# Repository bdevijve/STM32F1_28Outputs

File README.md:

# STM32F1_28Outputs
Carte domotique de Gaël - STM32F103VET6 - 28 sorties NPN 5-24V

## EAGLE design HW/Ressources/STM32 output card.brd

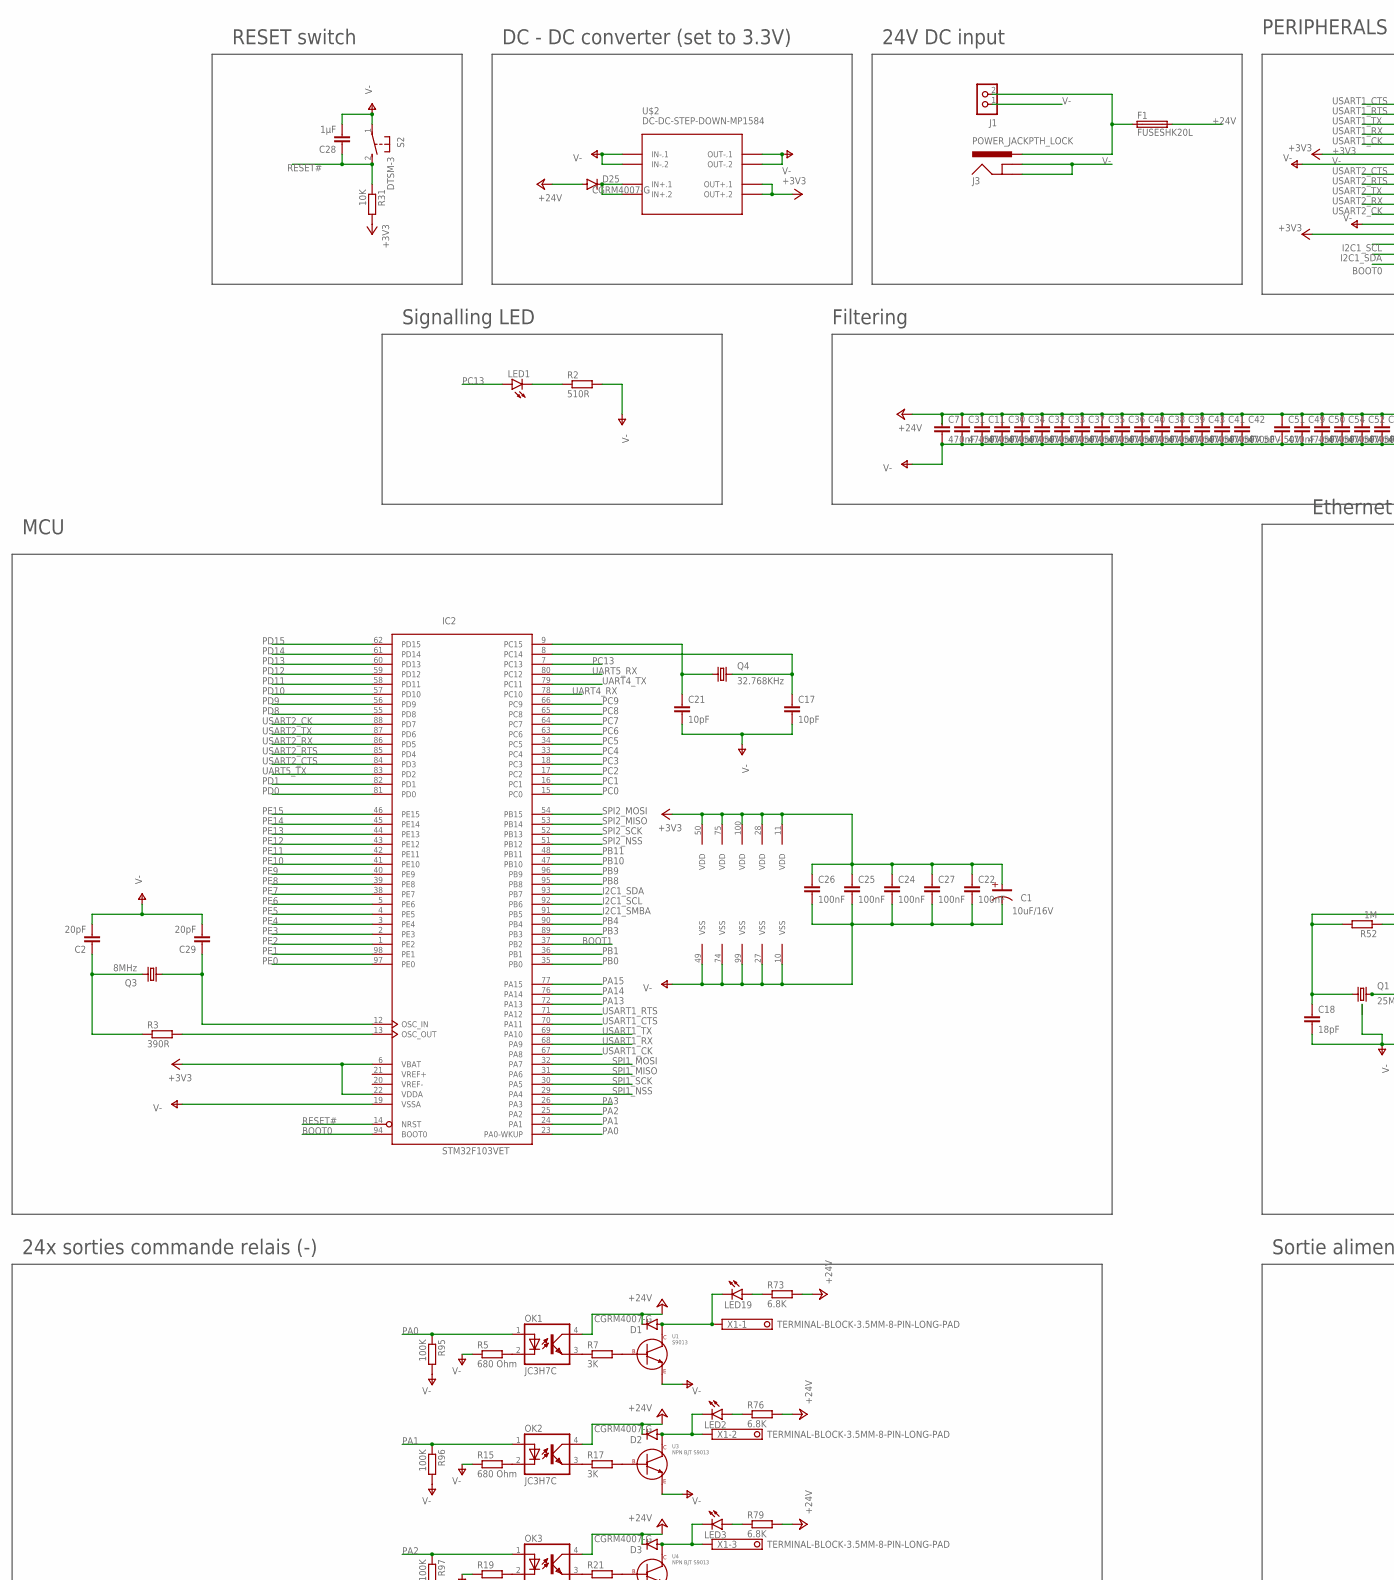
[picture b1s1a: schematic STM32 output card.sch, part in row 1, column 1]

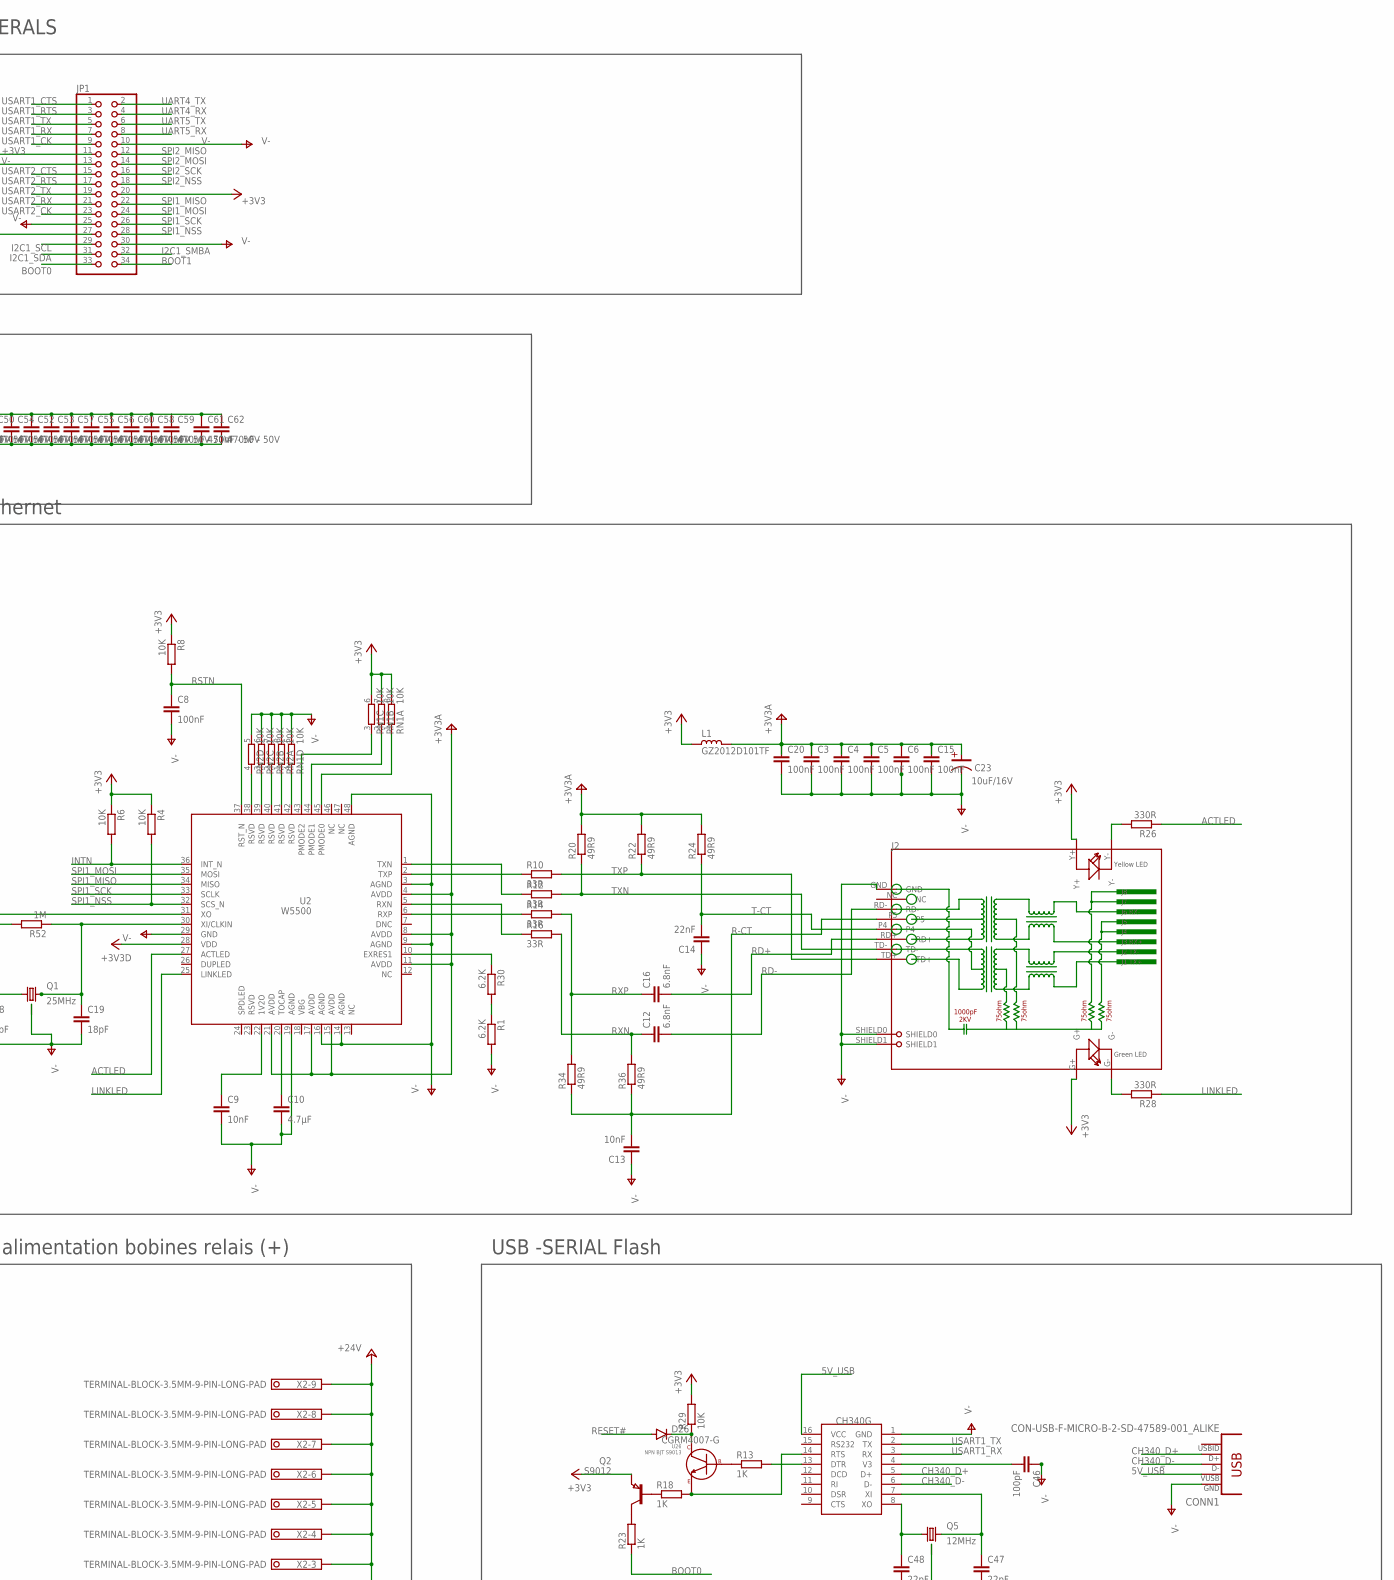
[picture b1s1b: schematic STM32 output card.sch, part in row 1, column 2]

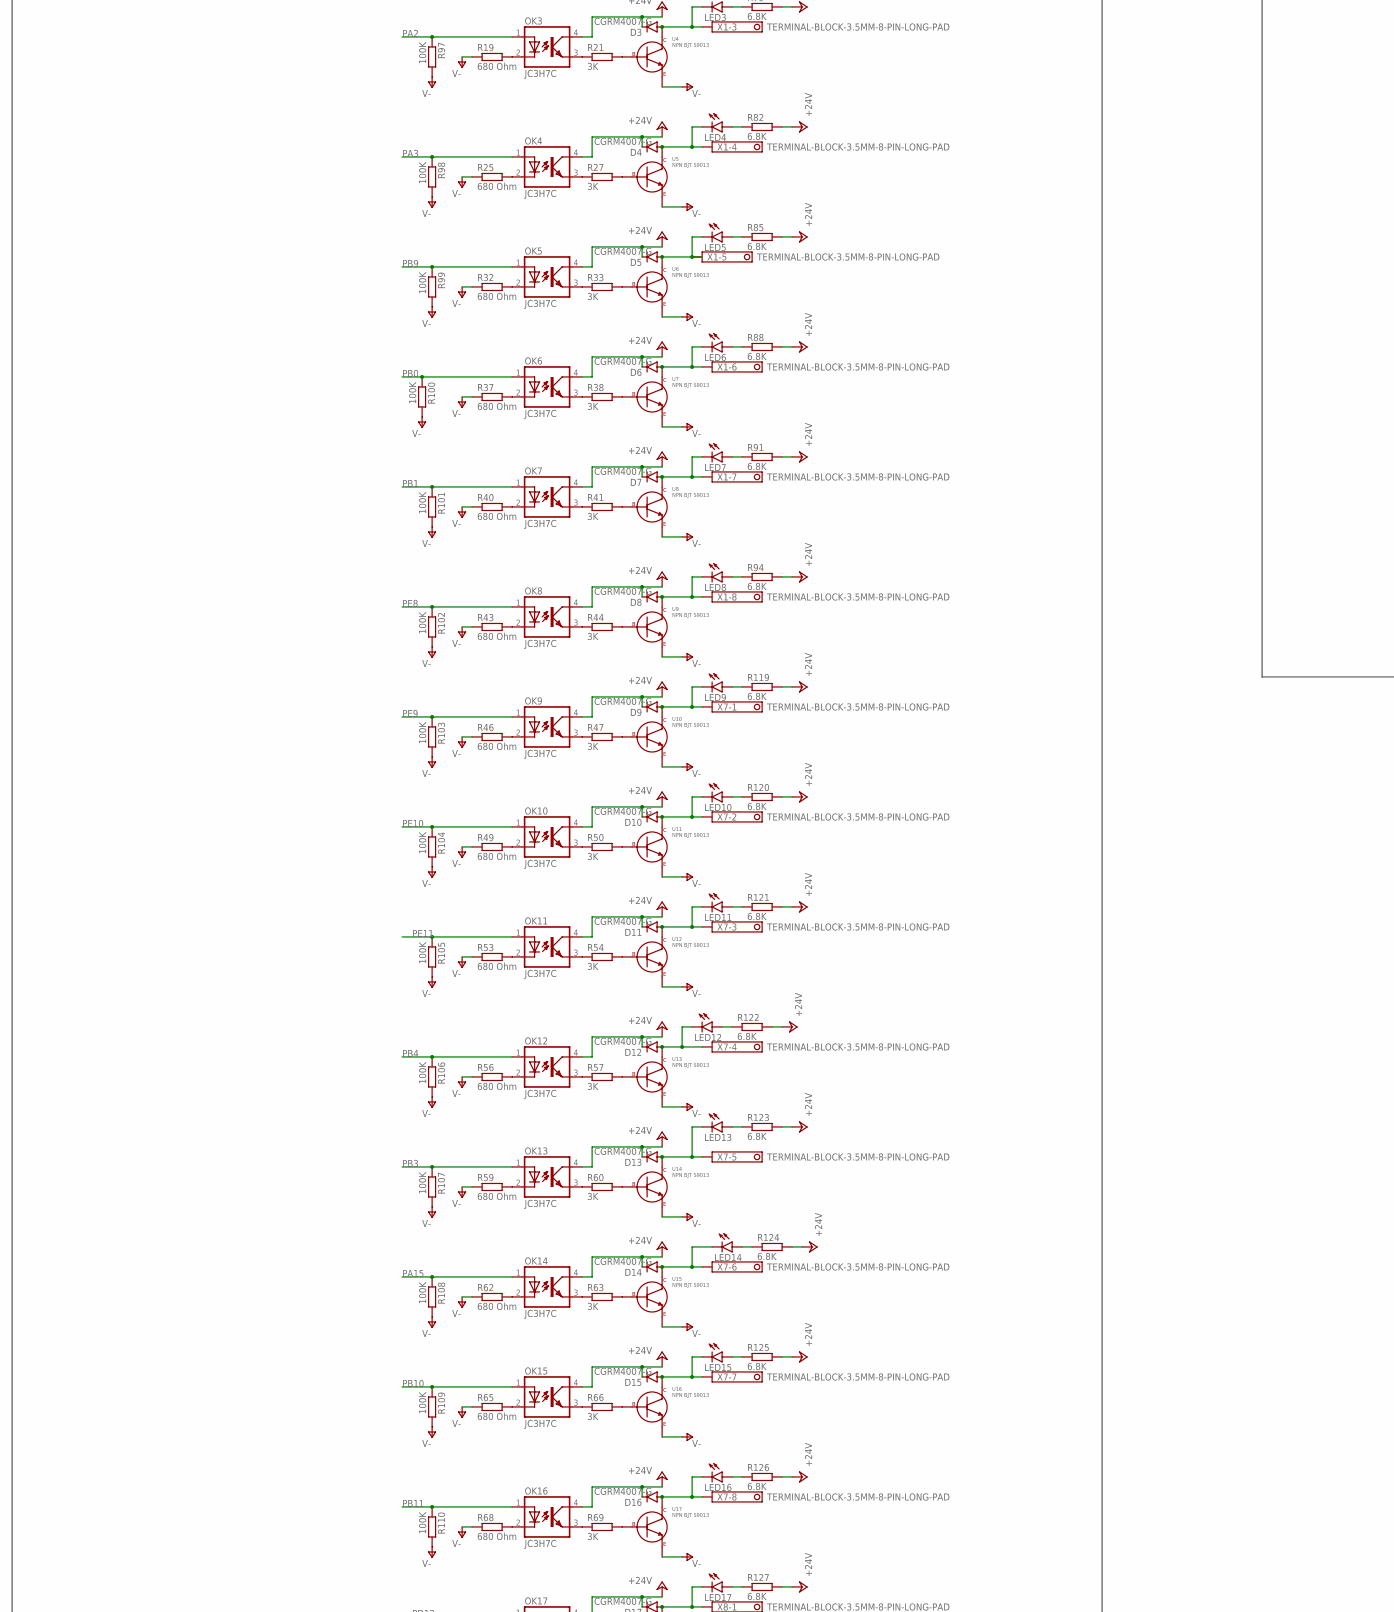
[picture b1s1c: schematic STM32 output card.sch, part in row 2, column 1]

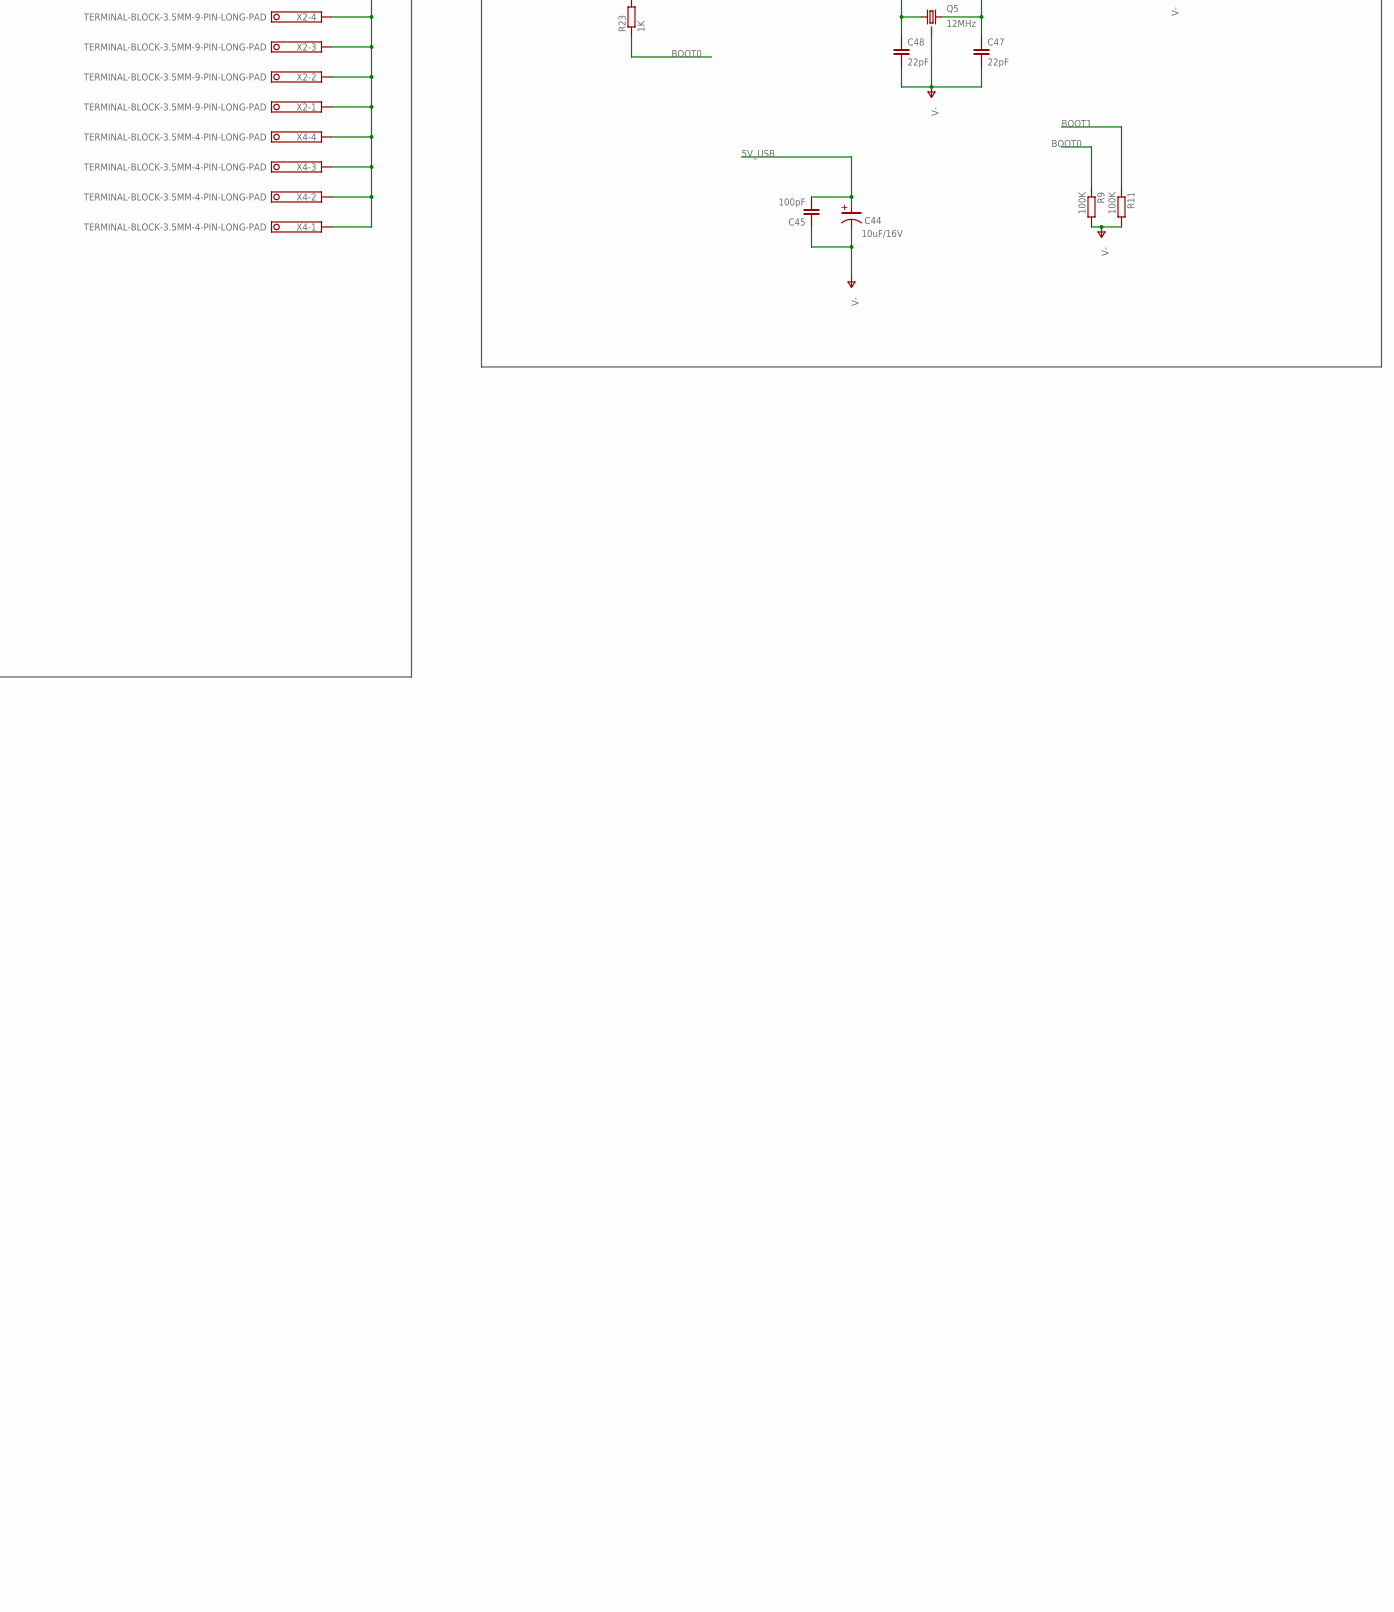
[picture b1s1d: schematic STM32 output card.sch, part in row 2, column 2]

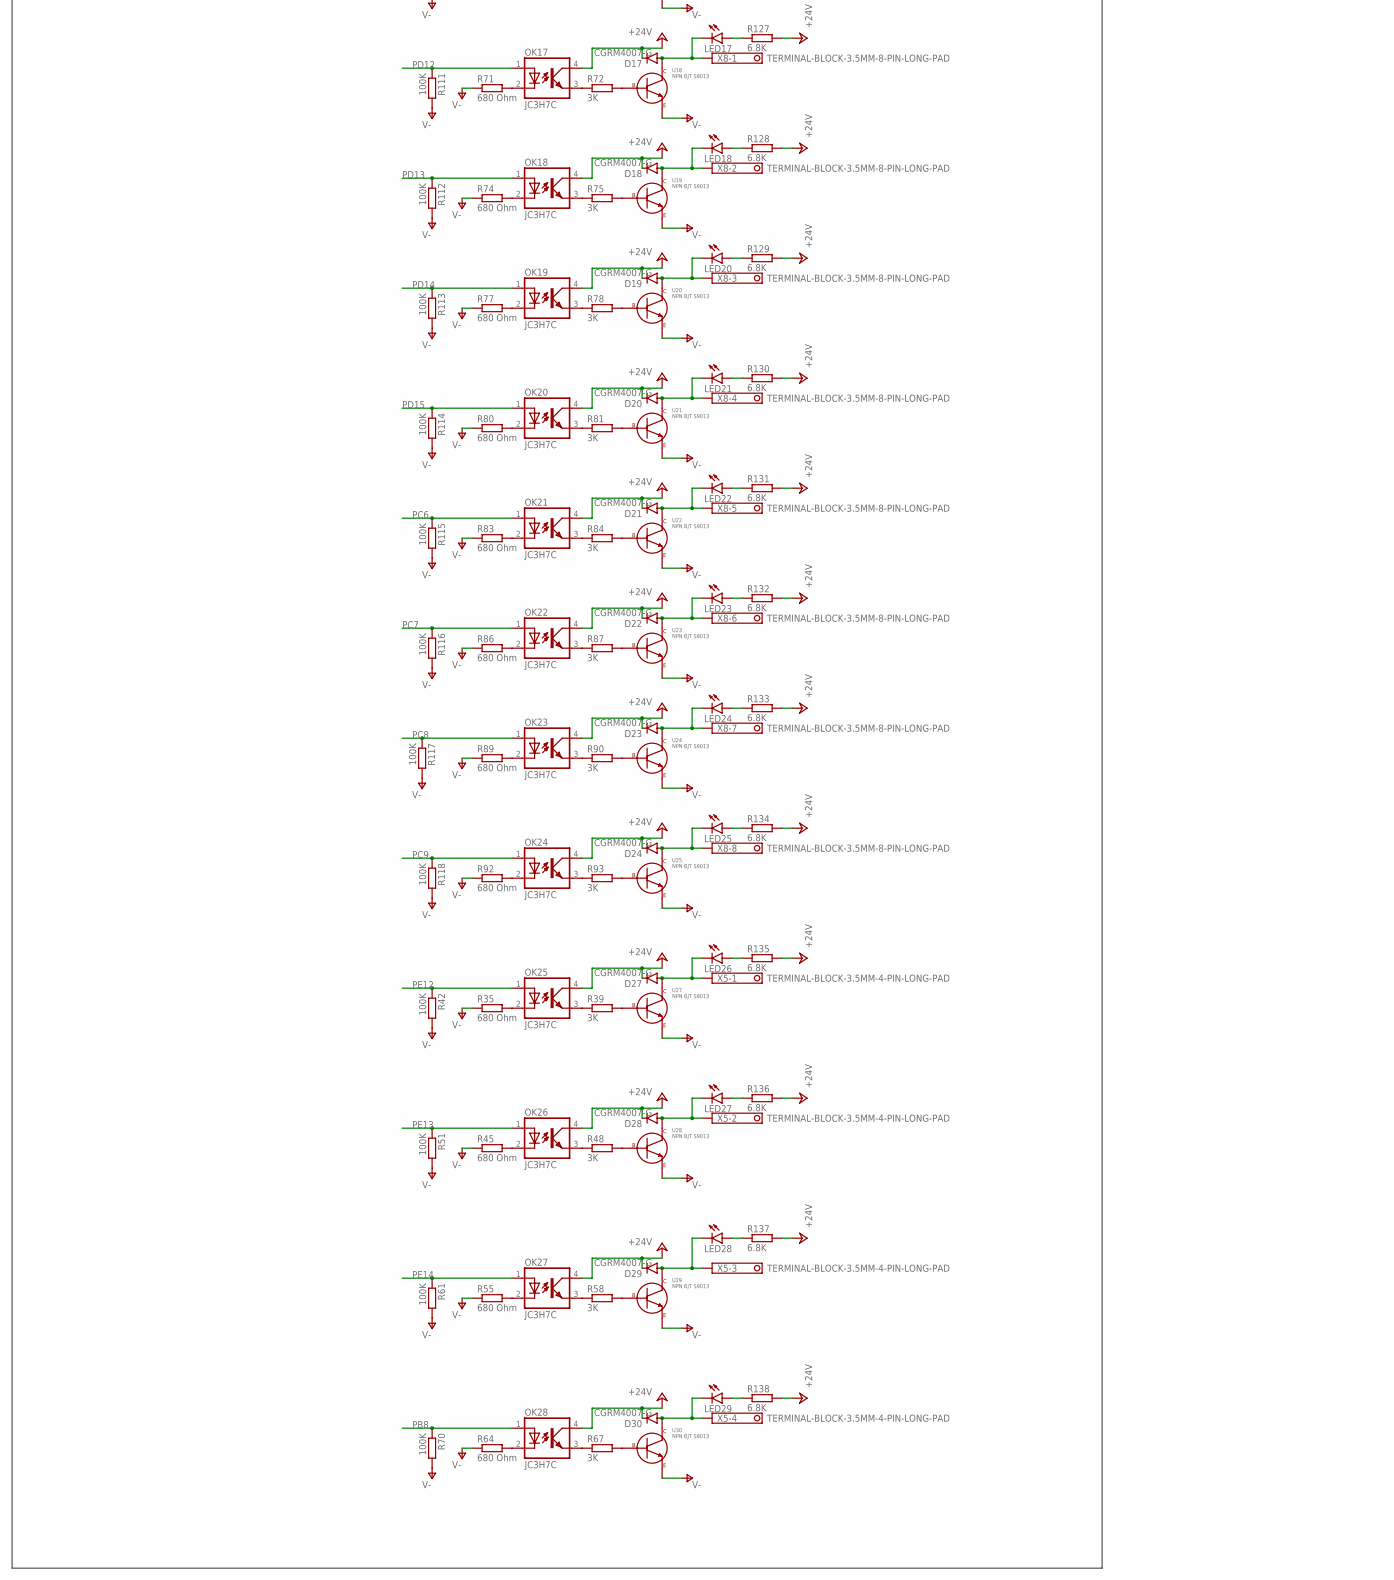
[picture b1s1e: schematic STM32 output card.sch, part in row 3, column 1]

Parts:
C1, C23, C44: 10uF/16V; C-3216(TANTAL)
C2, C29: 20pF; C0402
C3, C4, C5, C6, C8, C15, C20, C22, C24, C25, C26, C27: 100nF; C0402
C7, C11, C30, C31, C32, C33, C34, C35, C36, C37, C38, C39, C40, C41, C42, C43, C49, C50, C51, C52, C53, C54, C55, C56, C57, C58, C59, C60, C61, C62: 470nF - 50V; C0805
C9, C13: 10nF; C0402
C10: 4.7µF; C0402
C12, C16: 6.8nF; C0402
C14: 22nF; C0402
C17, C21: 10pF; C0402
C18, C19: 18pF; C0402
C28: 1µF; C0402
C45, C46: 100pF; C0402
C47, C48: 22pF; C0402
CONN1: CON-USB-F-MICRO-B-2-SD-47589-001_ALIKE; CON_USB_MICRO-B-3
D1, D2, D3, D4, D5, D6, D7, D8, D9, D10, D11, D12, D13, D14, D15, D16, D17, D18, D19, D20, D21, D22, D23, D24, D25, D26, D27, D28, D29, D30: CGRM4007-G; SOD-123_MINI-SMA
F1: FUSESHK20L; SHK20L
IC2: STM32F103VET; LQFP100
J1: CON_TERMINAL_BLOCK_02-5MM; TERMINAL_BLOCK_2P_5
J2: RJ45-HR911105A-HR911105A; RJ45
J3: POWER_JACKPTH_LOCK; POWER_JACK_PTH_LOCK
JP1: PINHD-2X17; 2X17
L1: GZ2012D101TF; L0805
LED1: LEDCHIP-LED0603; CHIP-LED0603
LED2, LED3, LED4, LED5, LED6, LED7, LED8, LED9, LED10, LED11, LED12, LED13, LED14, LED15, LED16, LED17, LED18, LED19, LED20, LED21, LED22, LED23, LED24, LED25, LED26, LED27, LED28, LED29: LEDSML0603; SML0603
OK1, OK2, OK3, OK4, OK5, OK6, OK7, OK8, OK9, OK10, OK11, OK12, OK13, OK14, OK15, OK16, OK17, OK18, OK19, OK20, OK21, OK22, OK23, OK24, OK25, OK26, OK27, OK28: JC3H7C; MINI-FLAT-4
Q1: 25MHz; 3.2X2.5_KX-7
Q2: S9012; SOT23
Q3: 8MHz; 5.0X3.2_2
Q4: 32.768KHz; 3.2X1.5
Q5: 12MHz; 3.2X2.5_KX-7
R1, R30: 6.2K; R0603
R2: 510R; R0402
R3: 390R; R0603
R4, R6, R8, R29, R31: 10K; R0402
R5, R15, R19, R25, R32, R35, R37, R40, R43, R45, R46, R49, R53, R55, R56, R59, R62, R64, R65, R68, R71, R74, R77, R80, R83, R86, R89, R92: 680 Ohm; R0402
R7, R17, R21, R27, R33, R38, R39, R41, R44, R47, R48, R50, R54, R57, R58, R60, R63, R66, R67, R69, R72, R75, R78, R81, R84, R87, R90, R93: 3K; R0805
R9, R11, R42, R51, R61, R70, R95, R96, R97, R98, R99, R100, R101, R102, R103, R104, R105, R106, R107, R108, R109, R110, R111, R112, R113, R114, R115, R116, R117, R118: 100K; R0402
R10, R12, R14, R16: 33R; R0805
R13, R18, R23: 1K; R0402
R20, R22, R24, R34, R36: 49R9; R0805
R26, R28: 330R; R0402
R52: 1M; R0402
R73, R76, R79, R82, R85, R88, R91, R94, R119, R120, R121, R122, R123, R124, R125, R126, R127, R128, R129, R130, R131, R132, R133, R134, R135, R136, R137, R138: 6.8K; R0402
RN1, RN2: 10K; 4X0402ARV341
S2: DTSM-3
U1: S9013; SOT-23-3; MPN MF-DSC-SOT233-MMBT5551
U2: W5500
U3, U4, U5, U6, U7, U8, U9, U10, U11, U12, U13, U14, U15, U16, U17, U18, U19, U20, U21, U22, U23, U24, U25, U26, U27, U28, U29, U30: NPN BJT S9013; SOT-23-3
U$1: CH340G; SOIC16
U$2: DC-DC-STEP-DOWN-MP1584
X1, X7, X8: TERMINAL-BLOCK-3.5MM-8-PIN-LONG-PAD; TERMINAL-BLOCK-8-PIN-3.5MM-LONG-PAD
X2: TERMINAL-BLOCK-3.5MM-9-PIN-LONG-PAD; TERMINAL-BLOCK-9-PIN-3.5MM-LONG-PAD
X4, X5: TERMINAL-BLOCK-3.5MM-4-PIN-LONG-PAD; TERMINAL-BLOCK-4-PIN-3.5MM-LONG-PAD

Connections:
5V_USB: C44.1, C45.2, CONN1.P1 (VUSB), U$1.16 (VCC)
+3V3: C1.1, C22.1, C24.1, C25.1, C26.1, C27.1, IC2.6 (VBAT), IC2.11 (VDD), IC2.22 (VDDA), IC2.28 (VDD), IC2.50 (VDD), IC2.75 (VDD), IC2.100 (VDD), J2.G+, J2.Y+, JP1.11, JP1.20, JP1.27, L1.2, Q2.2 (E), R4.1, R6.1, R8.1, R29.2, R31.2, RN1.6 (2), RN1.7 (2), RN1.8 (2), U2.28 (VDD), U$2.OUT+.1, U$2.OUT+.2
+3V3A: C3.1, C4.1, C5.1, C6.1, C15.1, C20.1, C23.1, L1.1, R20.2, R22.2, R24.2, U2.4 (AVDD), U2.8 (AVDD), U2.11 (AVDD), U2.15 (AVDD), U2.17 (AVDD), U2.21 (AVDD)
+24V: C7.1, C11.1, C30.1, C31.1, C32.1, C33.1, C34.1, C35.1, C36.1, C37.1, C38.1, C39.1, C40.1, C41.1, C42.1, C43.1, C49.1, C50.1, C51.1, C52.1, C53.1, C54.1, C55.1, C56.1, C57.1, C58.1, C59.1, C60.1, C61.1, C62.1, D1.C, D2.C, D3.C, D4.C, D5.C, D6.C, D7.C, D8.C, D9.C, D10.C, D11.C, D12.C, D13.C, D14.C, D15.C, D16.C, D17.C, D18.C, D19.C, D20.C, D21.C, D22.C, D23.C, D24.C, D25.A, D27.C, D28.C, D29.C, D30.C, F1.2A (2), OK1.4 (COL), OK2.4 (COL), OK3.4 (COL), OK4.4 (COL), OK5.4 (COL), OK6.4 (COL), OK7.4 (COL), OK8.4 (COL), OK9.4 (COL), OK10.4 (COL), OK11.4 (COL), OK12.4 (COL), OK13.4 (COL), OK14.4 (COL), OK15.4 (COL), OK16.4 (COL), OK17.4 (COL), OK18.4 (COL), OK19.4 (COL), OK20.4 (COL), OK21.4 (COL), OK22.4 (COL), OK23.4 (COL), OK24.4 (COL), OK25.4 (COL), OK26.4 (COL), OK27.4 (COL), OK28.4 (COL), R73.2, R76.2, R79.2, R82.2, R85.2, R88.2, R91.2, R94.2, R119.2, R120.2, R121.2, R122.2, R123.2, R124.2, R125.2, R126.2, R127.2, R128.2, R129.2, R130.2, R131.2, R132.2, R133.2, R134.2, R135.2, R136.2, R137.2, R138.2, X2.1, X2.2, X2.3, X2.4, X2.5, X2.6, X2.7, X2.8, X2.9, X4.1, X4.2, X4.3, X4.4
ACTLED: R26.1, U2.27 (ACTLED)
BOOT0: IC2.94 (BOOT0), JP1.33, R9.1, R23.1
BOOT1: IC2.37 (PB2), JP1.34, R11.1
CH340_D+: CONN1.P3 (D+), U$1.5 (D+)
CH340_D-: CONN1.P2 (D-), U$1.6 (D-)
I2C1_SCL: IC2.92 (PB6), JP1.29
I2C1_SDA: IC2.93 (PB7), JP1.31
I2C1_SMBA: IC2.91 (PB5), JP1.32
INTN: R6.2, U2.36 (INT_N)
LINKLED: R28.1, U2.25 (LINKLED)
unnamed: OK1.2 (C), R5.2
unnamed: LED1.C, R2.1
unnamed: C2.1, Q3.2, R3.1
unnamed: C17.1, IC2.8 (PC14), Q4.2
unnamed: D25.C, U$2.IN+.1, U$2.IN+.2
unnamed: C21.1, IC2.9 (PC15), Q4.1
unnamed: C29.1, IC2.12 (OSC_IN), Q3.1
unnamed: IC2.13 (OSC_OUT), R3.2
unnamed: OK1.3 (EMIT), R7.1
unnamed: R7.2, U1.P$1 (BASE)
unnamed: LED2.A, R76.1
unnamed: LED19.A, R73.1
unnamed: OK25.3 (EMIT), R39.1
unnamed: OK2.3 (EMIT), R17.1
unnamed: R17.2, U3.P$1 (BASE)
unnamed: OK2.2 (C), R15.2
unnamed: RN2.4 (1), U2.38 (RSVD)
unnamed: R18.2, U26.P$2 (EMITTER), U$1.14 (RTS)
unnamed: OK3.3 (EMIT), R21.1
unnamed: R21.2, U4.P$1 (BASE)
unnamed: OK3.2 (C), R19.2
unnamed: F1.1A (1), J1.2, J3.PWR
unnamed: OK4.3 (EMIT), R27.1
unnamed: R27.2, U5.P$1 (BASE)
unnamed: OK4.2 (C), R25.2
unnamed: C47.1, Q5.3 (2), U$1.7 (XI)
unnamed: OK5.3 (EMIT), R33.1
unnamed: R33.2, U6.P$1 (BASE)
unnamed: OK5.2 (C), R32.2
unnamed: C46.2, U$1.4 (V3)
unnamed: OK6.3 (EMIT), R38.1
unnamed: R38.2, U7.P$1 (BASE)
unnamed: OK6.2 (C), R37.2
unnamed: R13.2, U$1.13 (DTR)
unnamed: OK7.3 (EMIT), R41.1
unnamed: R41.2, U8.P$1 (BASE)
unnamed: OK7.2 (C), R40.2
unnamed: C48.1, Q5.1, U$1.8 (XO)
unnamed: OK8.3 (EMIT), R44.1
unnamed: R44.2, U9.P$1 (BASE)
unnamed: OK8.2 (C), R43.2
unnamed: R13.1, U26.P$1 (BASE)
unnamed: OK9.3 (EMIT), R47.1
unnamed: R47.2, U10.P$1 (BASE)
unnamed: OK9.2 (C), R46.2
unnamed: RN2.3 (1), U2.39 (RSVD)
unnamed: Q2.1 (B), R18.1
unnamed: RN2.2 (1), U2.40 (RSVD)
unnamed: OK10.3 (EMIT), R50.1
unnamed: RN2.1, U2.41 (RSVD)
unnamed: R50.2, U11.P$1 (BASE)
unnamed: RN1.4 (1), U2.42 (RSVD)
unnamed: OK10.2 (C), R49.2
unnamed: Q2.3 (C), R23.2
unnamed: OK11.3 (EMIT), R54.1
unnamed: R54.2, U12.P$1 (BASE)
unnamed: OK11.2 (C), R53.2
unnamed: D26.C, R29.1, U26.P$3 (COLLECTOR)
unnamed: OK12.3 (EMIT), R57.1
unnamed: R57.2, U13.P$1 (BASE)
unnamed: OK12.2 (C), R56.2
unnamed: R39.2, U27.P$1 (BASE)
unnamed: OK13.3 (EMIT), R60.1
unnamed: R60.2, U14.P$1 (BASE)
unnamed: OK13.2 (C), R59.2
unnamed: OK14.3 (EMIT), R63.1
unnamed: R63.2, U15.P$1 (BASE)
unnamed: OK14.2 (C), R62.2
unnamed: J2.Y-, R26.2
unnamed: OK25.2 (C), R35.2
unnamed: OK15.3 (EMIT), R66.1
unnamed: R66.2, U16.P$1 (BASE)
unnamed: OK15.2 (C), R65.2
unnamed: OK26.3 (EMIT), R48.1
unnamed: OK16.3 (EMIT), R69.1
unnamed: R69.2, U17.P$1 (BASE)
unnamed: OK16.2 (C), R68.2
unnamed: R48.2, U28.P$1 (BASE)
unnamed: OK17.3 (EMIT), R72.1
unnamed: J2.G-, R28.2
unnamed: R72.2, U18.P$1 (BASE)
unnamed: R1.1, R30.2
unnamed: OK17.2 (C), R71.2
unnamed: OK18.3 (EMIT), R75.1
unnamed: R75.2, U19.P$1 (BASE)
unnamed: OK18.2 (C), R74.2
unnamed: OK26.2 (C), R45.2
unnamed: OK19.3 (EMIT), R78.1
unnamed: R78.2, U20.P$1 (BASE)
unnamed: OK19.2 (C), R77.2
unnamed: OK27.3 (EMIT), R58.1
unnamed: OK20.3 (EMIT), R81.1
unnamed: R81.2, U21.P$1 (BASE)
unnamed: OK20.2 (C), R80.2
unnamed: R58.2, U29.P$1 (BASE)
unnamed: OK21.3 (EMIT), R84.1
unnamed: R84.2, U22.P$1 (BASE)
unnamed: OK21.2 (C), R83.2
unnamed: OK22.3 (EMIT), R87.1
unnamed: R87.2, U23.P$1 (BASE)
unnamed: OK22.2 (C), R86.2
unnamed: OK27.2 (C), R55.2
unnamed: OK23.3 (EMIT), R90.1
unnamed: R90.2, U24.P$1 (BASE)
unnamed: OK23.2 (C), R89.2
unnamed: OK28.3 (EMIT), R67.1
unnamed: OK24.3 (EMIT), R93.1
unnamed: R93.2, U25.P$1 (BASE)
unnamed: OK24.2 (C), R92.2
unnamed: R67.2, U30.P$1 (BASE)
unnamed: OK28.2 (C), R64.2
unnamed: D1.A, LED19.C, U1.P$3 (COLLECTOR), X1.1
unnamed: D2.A, LED2.C, U3.P$3 (COLLECTOR), X1.2
unnamed: LED3.A, R79.1
unnamed: D3.A, LED3.C, U4.P$3 (COLLECTOR), X1.3
unnamed: LED4.A, R82.1
unnamed: D4.A, LED4.C, U5.P$3 (COLLECTOR), X1.4
unnamed: LED5.A, R85.1
unnamed: D5.A, LED5.C, U6.P$3 (COLLECTOR), X1.5
unnamed: LED6.A, R88.1
unnamed: D6.A, LED6.C, U7.P$3 (COLLECTOR), X1.6
unnamed: LED7.A, R91.1
unnamed: D7.A, LED7.C, U8.P$3 (COLLECTOR), X1.7
unnamed: LED8.A, R94.1
unnamed: D8.A, LED8.C, U9.P$3 (COLLECTOR), X1.8
unnamed: LED9.A, R119.1
unnamed: D9.A, LED9.C, U10.P$3 (COLLECTOR), X7.1
unnamed: LED10.A, R120.1
unnamed: D10.A, LED10.C, U11.P$3 (COLLECTOR), X7.2
unnamed: LED11.A, R121.1
unnamed: D11.A, LED11.C, U12.P$3 (COLLECTOR), X7.3
unnamed: LED12.A, R122.1
unnamed: D12.A, LED12.C, U13.P$3 (COLLECTOR), X7.4
unnamed: LED13.A, R123.1
unnamed: D13.A, LED13.C, U14.P$3 (COLLECTOR), X7.5
unnamed: LED14.A, R124.1
unnamed: D14.A, LED14.C, U15.P$3 (COLLECTOR), X7.6
unnamed: LED15.A, R125.1
unnamed: D15.A, LED15.C, U16.P$3 (COLLECTOR), X7.7
unnamed: LED16.A, R126.1
unnamed: D16.A, LED16.C, U17.P$3 (COLLECTOR), X7.8
unnamed: LED17.A, R127.1
unnamed: D17.A, LED17.C, U18.P$3 (COLLECTOR), X8.1
unnamed: LED18.A, R128.1
unnamed: D18.A, LED18.C, U19.P$3 (COLLECTOR), X8.2
unnamed: LED20.A, R129.1
unnamed: D19.A, LED20.C, U20.P$3 (COLLECTOR), X8.3
unnamed: LED21.A, R130.1
unnamed: D20.A, LED21.C, U21.P$3 (COLLECTOR), X8.4
unnamed: LED22.A, R131.1
unnamed: D21.A, LED22.C, U22.P$3 (COLLECTOR), X8.5
unnamed: LED23.A, R132.1
unnamed: D22.A, LED23.C, U23.P$3 (COLLECTOR), X8.6
unnamed: LED24.A, R133.1
unnamed: D23.A, LED24.C, U24.P$3 (COLLECTOR), X8.7
unnamed: LED25.A, R134.1
unnamed: D24.A, LED25.C, U25.P$3 (COLLECTOR), X8.8
unnamed: LED26.A, R135.1
unnamed: D27.A, LED26.C, U27.P$3 (COLLECTOR), X5.1
unnamed: LED27.A, R136.1
unnamed: D28.A, LED27.C, U28.P$3 (COLLECTOR), X5.2
unnamed: LED28.A, R137.1
unnamed: D29.A, LED28.C, U29.P$3 (COLLECTOR), X5.3
unnamed: LED29.A, R138.1
unnamed: D30.A, LED29.C, U30.P$3 (COLLECTOR), X5.4
unnamed: RN1.3 (1), U2.43 (PMODE2)
unnamed: RN1.2 (1), U2.44 (PMODE1)
unnamed: RN1.1, U2.45 (PMODE0)
unnamed: C10.1, U2.20 (TOCAP)
unnamed: C9.1, U2.22 (1V2O)
unnamed: R30.1, U2.10 (EXRES1)
unnamed: C18.1, Q1.1, R52.2, U2.31 (XO)
unnamed: R14.1, U2.6 (RXP)
unnamed: R16.1, U2.5 (RXN)
unnamed: R10.1, U2.2 (TXP)
unnamed: R12.1, U2.1 (TXN)
unnamed: C19.1, Q1.3 (2), R52.1, U2.30 (XI/CLKIN)
PA0: IC2.23 (PA0-WKUP), OK1.1 (A), R95.1
PA1: IC2.24 (PA1), OK2.1 (A), R96.1
PA2: IC2.25 (PA2), OK3.1 (A), R97.1
PA3: IC2.26 (PA3), OK4.1 (A), R98.1
PA13: IC2.72 (PA13)
PA14: IC2.76 (PA14)
PA15: IC2.77 (PA15), OK14.1 (A), R108.1
PB0: IC2.35 (PB0), OK6.1 (A), R100.1
PB1: IC2.36 (PB1), OK7.1 (A), R101.1
PB3: IC2.89 (PB3), OK13.1 (A), R107.1
PB4: IC2.90 (PB4), OK12.1 (A), R106.1
PB8: IC2.95 (PB8), OK28.1 (A), R70.1
PB9: IC2.96 (PB9), OK5.1 (A), R99.1
PB10: IC2.47 (PB10), OK15.1 (A), R109.1
PB11: IC2.48 (PB11), OK16.1 (A), R110.1
PC0: IC2.15 (PC0)
PC1: IC2.16 (PC1)
PC2: IC2.17 (PC2)
PC3: IC2.18 (PC3)
PC4: IC2.33 (PC4)
PC5: IC2.34 (PC5)
PC6: IC2.63 (PC6), OK21.1 (A), R115.1
PC7: IC2.64 (PC7), OK22.1 (A), R116.1
PC8: IC2.65 (PC8), OK23.1 (A), R117.1
PC9: IC2.66 (PC9), OK24.1 (A), R118.1
PC13: IC2.7 (PC13), LED1.A
PD0: IC2.81 (PD0)
PD1: IC2.82 (PD1)
PD8: IC2.55 (PD8)
PD9: IC2.56 (PD9)
PD10: IC2.57 (PD10)
PD11: IC2.58 (PD11)
PD12: IC2.59 (PD12), OK17.1 (A), R111.1
PD13: IC2.60 (PD13), OK18.1 (A), R112.1
PD14: IC2.61 (PD14), OK19.1 (A), R113.1
PD15: IC2.62 (PD15), OK20.1 (A), R114.1
PE0: IC2.97 (PE0)
PE1: IC2.98 (PE1)
PE2: IC2.1 (PE2)
PE3: IC2.2 (PE3)
PE4: IC2.3 (PE4)
PE5: IC2.4 (PE5)
PE6: IC2.5 (PE6)
PE7: IC2.38 (PE7)
PE8: IC2.39 (PE8), OK8.1 (A), R102.1
PE9: IC2.40 (PE9), OK9.1 (A), R103.1
PE10: IC2.41 (PE10), OK10.1 (A), R104.1
PE11: IC2.42 (PE11), OK11.1 (A), R105.1
PE12: IC2.43 (PE12), OK25.1 (A), R42.1
PE13: IC2.44 (PE13), OK26.1 (A), R51.1
PE14: IC2.45 (PE14), OK27.1 (A), R61.1
PE15: IC2.46 (PE15)
R-CT: C13.2, J2.P5, R34.1, R36.1
RD+: C16.2, J2.RD+
RD-: C12.2, J2.RD-
RESET#: C28.1, D26.A, IC2.14 (NRST), R31.1, S2.2
RSTN: C8.1, R8.2, U2.37 (RST_N)
RXN: C12.1, R16.2, R36.2
RXP: C16.1, R14.2, R34.2
SPI1_MISO: IC2.31 (PA6), JP1.22, U2.34 (MISO)
SPI1_MOSI: IC2.32 (PA7), JP1.24, U2.35 (MOSI)
SPI1_NSS: IC2.29 (PA4), JP1.28, R4.2, U2.32 (SCS_N)
SPI1_SCK: IC2.30 (PA5), JP1.26, U2.33 (SCLK)
SPI2_MISO: IC2.53 (PB14), JP1.12
SPI2_MOSI: IC2.54 (PB15), JP1.14
SPI2_NSS: IC2.51 (PB12), JP1.18
SPI2_SCK: IC2.52 (PB13), JP1.16
T-CT: C14.2, J2.P4, R24.1
TXN: J2.TD-, R12.2, R20.1
TXP: J2.TD+, R10.2, R22.1
UART4_RX: IC2.78 (PC10), JP1.4
UART4_TX: IC2.79 (PC11), JP1.2
UART5_RX: IC2.80 (PC12), JP1.8
UART5_TX: IC2.83 (PD2), JP1.6
USART1_CK: IC2.67 (PA8), JP1.9
USART1_CTS: IC2.70 (PA11), JP1.1
USART1_RTS: IC2.71 (PA12), JP1.3
USART1_RX: IC2.68 (PA9), JP1.7, U$1.3 (RX)
USART1_TX: IC2.69 (PA10), JP1.5, U$1.2 (TX)
USART2_CK: IC2.88 (PD7), JP1.23
USART2_CTS: IC2.84 (PD3), JP1.15
USART2_RTS: IC2.85 (PD4), JP1.17
USART2_RX: IC2.86 (PD5), JP1.21
USART2_TX: IC2.87 (PD6), JP1.19
V-: C1.2, C2.2, C3.2, C4.2, C5.2, C6.2, C7.2, C8.2, C9.2, C10.2, C11.2, C13.1, C14.1, C15.2, C17.2, C18.2, C19.2, C20.2, C21.2, C22.2, C23.2, C24.2, C25.2, C26.2, C27.2, C28.2, C29.2, C30.2, C31.2, C32.2, C33.2, C34.2, C35.2, C36.2, C37.2, C38.2, C39.2, C40.2, C41.2, C42.2, C43.2, C44.2, C45.1, C46.1, C47.2, C48.2, C49.2, C50.2, C51.2, C52.2, C53.2, C54.2, C55.2, C56.2, C57.2, C58.2, C59.2, C60.2, C61.2, C62.2, CONN1.P5 (GND), IC2.10 (VSS), IC2.19 (VSSA), IC2.27 (VSS), IC2.49 (VSS), IC2.74 (VSS), IC2.99 (VSS), J1.1, J2.GND, J2.SHIELD0, J2.SHIELD1, J3.GND, J3.GNDBREAK, JP1.10, JP1.13, JP1.25, JP1.30, Q1.2, Q1.4, Q5.2, Q5.4, R1.2, R2.2, R5.1, R9.2, R11.2, R15.1, R19.1, R25.1, R32.1, R35.1, R37.1, R40.1, R42.2, R43.1, R45.1, R46.1, R49.1, R51.2, R53.1, R55.1, R56.1, R59.1, R61.2, R62.1, R64.1, R65.1, R68.1, R70.2, R71.1, R74.1, R77.1, R80.1, R83.1, R86.1, R89.1, R92.1, R95.2, R96.2, R97.2, R98.2, R99.2, R100.2, R101.2, R102.2, R103.2, R104.2, R105.2, R106.2, R107.2, R108.2, R109.2, R110.2, R111.2, R112.2, R113.2, R114.2, R115.2, R116.2, R117.2, R118.2, RN1.5 (2), RN2.5 (2), RN2.6 (2), RN2.7 (2), RN2.8 (2), S2.1, U1.P$2 (EMITTER), U2.3 (AGND), U2.9 (AGND), U2.14 (AGND), U2.16 (AGND), U2.19 (AGND), U2.29 (GND), U2.48 (AGND), U3.P$2 (EMITTER), U4.P$2 (EMITTER), U5.P$2 (EMITTER), U6.P$2 (EMITTER), U7.P$2 (EMITTER), U8.P$2 (EMITTER), U9.P$2 (EMITTER), U10.P$2 (EMITTER), U11.P$2 (EMITTER), U12.P$2 (EMITTER), U13.P$2 (EMITTER), U14.P$2 (EMITTER), U15.P$2 (EMITTER), U16.P$2 (EMITTER), U17.P$2 (EMITTER), U18.P$2 (EMITTER), U19.P$2 (EMITTER), U20.P$2 (EMITTER), U21.P$2 (EMITTER), U22.P$2 (EMITTER), U23.P$2 (EMITTER), U24.P$2 (EMITTER), U25.P$2 (EMITTER), U27.P$2 (EMITTER), U28.P$2 (EMITTER), U29.P$2 (EMITTER), U30.P$2 (EMITTER), U$1.1 (GND), U$2.IN-.1, U$2.IN-.2, U$2.OUT-.1, U$2.OUT-.2
VREF+: IC2.21 (VREF+)
VREF-: IC2.20 (VREF-)

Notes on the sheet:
DC - DC converter (set to 3.3V)
24V DC input
PERIPHERALS
RESET switch
Signalling LED
MCU
Ethernet
Filtering
Sortie alimentation bobines relais (+)
24x sorties commande relais (-)
USB -SERIAL Flash

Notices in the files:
parts and their libraries:
rc-master-smd: Copyright (C) 2007, Bob Starr
crystal-geyer_V1_0: Copyright: Geyer-Electronic
diy-modules: Released under the Creative Commons Attribution 4.0 International License: http://creativecommons.org/licenses/by/4.0
